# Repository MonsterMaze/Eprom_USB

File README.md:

# Eprom_USB
2716 through 27080 Eprom Programmer
A programmer for UV EPROMs with capacities between 2Kb (2716 series) and 1Mb (27C080 series).  
It uses an Arduino NANO and few other components.  
As a starting point I used the excelent [EpromProgrammer_ciprian-stingu](https://github.com/ciprian-stingu/EpromProgrammer) project

## Why this project?
I need write eproms for pinball machines and I have two not working
- Parallel port (epromwillem) windows XP 32b
- Serial port (PGM27) for DOS.

So, I need a new Eprom programmer with a USB port.
That is why I started this project
my OS is Ubuntu 24.04 - 64b right now.

## Main features
* It supports a large number of EPROMs with different capacities  
* 2 programming speeds (normal & fast). Fast programming speed is available if you configure the VCC correctly  
* On fast programming alghoritm, writing a 27C040 EPROM takes around 290 seconds  
* Error detection on writing  
* Additional verify option  

## GUI Software (Ubuntu Linux_x64)
Actualized "CMakeLists.txt" and code with AI help for Ubuntu 24.04 OS.  
New version 1.12 with 0.35v of voltage margin. (0.25v)
The complete source for project is in [soft_linux](soft_linux)  
I have compiled for Ubuntu 24.04 and is included in Release v1.12 folder [Release 1.12/AppImage](https://github.com/MonsterMaze/Eprom_USB/releases/download/Linux/Eprom_USB-x86_64.AppImage)  
With some changes for icons, locale, debug etc.  
Last version Linux  [soft_linux v2.26](soft_linux)  

## GUI Software (windows_x64)
Actualized "CMakeLists.txt" for Windows 11 OS.  
QTCreator project compiler with some few changes.  
The complete source for project is in [soft_Win64](soft_Win64)  
I have compiled in w11 and is included in Release v1.12 folder [Release 1.12/Eprom_USB_v1.0_Windows_x64.zip](https://github.com/MonsterMaze/Eprom_USB/releases/download/v1.12/Eprom_USB_v1.0_Windows_x64.zip)

## GUI Software (windows_x64) v2
I have some problems with serial Port in windows (!)  
so...  
Modify all project and name v2
The complete source for project is in [soft_Win64_v2](soft_Win64_v2)  
I have compiled in w11 and is included in Release v1.20 folder [Release 1.20/Eprom_USB_v2_Windows_x64.zip](https://github.com/MonsterMaze/Eprom_USB/releases/download/v1.12/Eprom_USB_v1.0_Windows_x64.zip)  
I test the exe in w7-64b and w11-64b.

## Eprom_USB v1.0.0 - Multiplatform Release
This release contains the standalone, portable binaries for the Eprom USB Programmer software,   
fully compatible with both Windows and Linux. No external installation or build tools are required.

### 🪟 Windows Instructions (64-bit)
1. Download **`Eprom_USB_v1.0_Windows_x64.zip`**.  
2. Extract the `.zip` file entirely into a folder of your choice.  
3. Double-click **`Eprom_USB.exe`** to launch the graphical interface.  
*Note: All required Qt, Gettext (`libintl`), and `libiconv` DLLs are included inside the package.*

### 🐧 Linux / Ubuntu Instructions (64-bit AppImage)
1. Download **`Eprom_USB-x86_64.AppImage`**.  
2. Open your terminal, navigate to the folder where you downloaded the file, and grant it execution permissions:  
   ```bash
   chmod +x Eprom_USB-x86_64.AppImage
   ```
3. Launch the application by double-clicking it or running:
   ```bash
   ./Eprom_USB-x86_64.AppImage
   ```

⚠️ **Important for Linux Users (Serial Port Permission):**
If the application cannot open or detect your USB serial port, your Linux user might lack dialout permissions.  
Fix this by running the following command once, then log out and log back into Ubuntu:
```bash
sudo usermod -a -G dialout \$USER
```

---
*Developed with Qt 5 and CMake. Built with native MinGW (Windows) and GCC (Linux) compiler suites.*

## Arduino Software
The sketch for arduino nano is here: [arduino_nano](arduino_nano)

## Hardware
New schematics and PCB into FreeCAD project, was modify for me are in [FreeCAD](FreeCAD) folder.  
I add LM317 for the Vpp power (12.5v - 12.75 - 21v - 25v) from 24Vac input  
For non KiCad users, schematics and PCB [hardware](hardware) in PDF format  
New v2 PCB made by Ivana, in PDF format [hardware/PCB_v2](hardware/PCB_v2) front, bottom and silk

## Images
The screenshots and images of PCB and others are available in [images](images) folder

## Supported EPROMs

### 2716 — 2 KB

| Manufacturer     | Part Number      |
|------------------|------------------|
| Generic          | 2716             |
| AMD              | 2716             |
| Intel            | 2716             |
| Hitachi          | HN462716         |
| Mitsubishi       | M5L2716K         |
| Fujitsu          | MBM2716          |
| Motorola         | MCM2716          |
| NEC              | µPD2716          |
| -                | ET2716           |
| -                | M2716            |

### 27C16 — 2 KB

| Manufacturer     | Part Number      |
|------------------|------------------|
| Generic          | 27C16            |
| National Semi    | 27C16            |
| AMD              | AM2716B          |
| National Semi    | NMC27C16B        |

### 2732 — 4 KB

| Manufacturer     | Part Number      |
|------------------|------------------|
| Generic          | 2732             |
| AMD              | AM2732           |
| AMD              | AM9732           |
| Fairchild        | F2732            |
| Hitachi          | HN462732         |
| Intel            | 2732A            |
| ST               | M2732A           |
| Fujitsu          | MBM2732          |
| NTE              | NTE2732A         |
| Toshiba          | TMM2732D         |
| NEC              | µPD2732A         |

### 27C32 — 4 KB

| Manufacturer     | Part Number      |
|------------------|------------------|
| Generic          | 27C32            |
| AMD              | AM2732B          |
| National Semi    | NMC27C32B        |
| WSI              | WS57C43C         |

### 2764 — 8 KB

| Manufacturer     | Part Number      |
|------------------|------------------|
| Generic          | 2764             |
| Intel            | 2764A            |
| ST               | M2764A           |
| Mitsubishi       | M5L2764K         |
| NTE              | NTE2764          |
| Toshiba          | TMM2764AD        |

### 27C64 — 8 KB

| Manufacturer     | Part Number      |
|------------------|------------------|
| Generic          | 27C64            |
| Microchip        | 27C64            |
| Cypress          | Cy7C266          |
| Fujitsu          | MBM27C64         |
| National Semi    | NMC27C64         |
| Texas Instruments| TMS27C64         |

### 27128 — 16 KB

| Manufacturer     | Part Number      |
|------------------|------------------|
| Generic          | 27128            |
| Hitachi          | HN4827128G       |
| Hitachi          | HN27128          |
| Intel            | M27128A          |
| ST               | M27128A          |
| Mitsubishi       | M5L27128K        |
| Mitsubishi       | M5M27C128K       |
| Fujitsu          | MBM27128         |
| NTE              | NTE21128         |
| Toshiba          | TMM27128AD       |
| Texas Instruments| TMS27128         |
| NEC              | µPD27128         |

### 27C128 — 16 KB

| Manufacturer     | Part Number      |
|------------------|------------------|
| Generic          | 27C128           |
| Microchip        | 27C128           |
| AMD              | AM27C128         |
| Atmel            | AT27C128         |
| Cypress          | CY27C128         |
| Sharp            | LH57126          |
| ST               | M27C128          |
| Oki              | MSM27C128        |
| Fairchild        | NM27C128         |
| National Semi    | NM27C128         |
| -                | QP27C128         |
| Texas Instruments| SMJ27C128        |
| Texas Instruments| TMS27C128        |

### 27256 — 32 KB

| Manufacturer     | Part Number      |
|------------------|------------------|
| Generic          | 27256            |
| -                | A68C256          |
| Atmel            | AT27256          |
| Intel            | 27256            |
| Mitsubishi       | M5L27256K        |
| Fujitsu          | MBM27256         |
| Oki              | MSM27256         |
| Toshiba          | TMM27256         |
| NEC              | µPD27256         |

### 27C256 — 32 KB

| Manufacturer     | Part Number      |
|------------------|------------------|
| Generic          | 27C256           |
| Microchip        | 27C256           |
| AMD              | AM27C256         |
| AMD              | AM27H256         |
| Sony             | CXK27C256DQ      |
| Cypress          | CY27C256         |
| Cypress          | CY27H256         |
| Cypress          | CY7C274          |
| -                | EM27C256         |
| -                | FM27C256         |
| Hitachi          | HN27C256A        |
| Hitachi          | HN27C256AG       |
| ISSI             | IS27C256         |
| ST               | M27C256B         |
| Mitsubishi       | M5M27C256K       |
| Fujitsu          | MBM27C256        |
| -                | 27HC256          |
| Oki              | MSM27C256H       |
| Fairchild        | NM27C256         |
| National Semi    | NM27C256         |
| National Semi    | NM27LC256        |
| National Semi    | NMC27C256        |
| National Semi    | NMC87C257        |
| -                | NPX27C256        |
| -                | QP27C256         |
| SEEQ             | 27C256           |
| SEEQ             | M27C256          |
| ASI              | SMJ27C256        |
| Texas Instruments| SMJ27C256        |
| -                | SPM27C256        |
| Toshiba          | TC57256          |
| Texas Instruments| TMS27C256        |
| Texas Instruments| TMS87C257        |
| NEC              | µPD27C256        |

### 27512 — 64 KB

| Manufacturer     | Part Number      |
|------------------|------------------|
| Generic          | 27512            |
| Intel            | 27512            |
| AMD              | AM27512          |
| Hitachi          | HN27512          |
| ST               | M27512           |
| Mitsubishi       | M5L27512K        |
| Oki              | MSM27512         |
| Toshiba          | TMM27512AD       |

### 27C512 — 64 KB

| Manufacturer     | Part Number      |
|------------------|------------------|
| Generic          | 27C512           |
| Microchip        | 27C512           |
| Intel            | 27C512           |
| Philips          | 27C512           |
| AMD              | AM27C512         |
| Sony             | CXK27C512DQ      |
| Cypress          | CY27C512         |
| Cypress          | CY27H512         |
| -                | EM27C512         |
| -                | FM27C512         |
| Hitachi          | HN27C512         |
| ISSI             | IS27HC512        |
| Fujitsu          | MBM27C512        |
| Macronix         | MX27C512         |
| National Semi    | NM27C512         |
| National Semi    | NM27P512         |
| ASI              | SMJ27C512        |
| Texas Instruments| SMJ27C512        |
| Toshiba          | TC57512AD        |
| Texas Instruments| TMS27C512        |
| NEC              | µPD27C512        |

### 27C010 — 128 KB

| Manufacturer     | Part Number      |
|------------------|------------------|
| Generic          | 27C010           |
| AMD              | AM27C010         |
| AMD              | AM27H010         |
| AMD              | AM27HB010        |
| Cypress          | CY27C010         |
| Cypress          | CY27H010         |
| Intel            | 27C010           |
| -                | EM27C010         |
| -                | FM27C010         |
| Hitachi          | HN27C101         |
| ISSI             | IS27C010         |
| Mitsubishi       | M5M27C101K       |
| Fairchild        | NM27C010         |
| National Semi    | NM27C010         |
| National Semi    | NMC27C010        |
| ASI              | SMJ27C010        |
| Texas Instruments| SMJ27C010        |
| Texas Instruments| TMS27C010        |

### 27C1001 — 128 KB

| Manufacturer     | Part Number      |
|------------------|------------------|
| Generic          | 27C1001          |
| Sony             | CXK27C1001DQ     |
| ST               | M27C1001         |
| Fujitsu          | MBM27C1001       |
| Oki              | MSM27C1000       |
| Macronix         | MX27C1000        |
| Toshiba          | TC57C1001        |
| Toshiba          | TC57H1001        |

### 27C020 — 256 KB

| Manufacturer     | Part Number      |
|------------------|------------------|
| Generic          | 27C020           |
| AMD              | AM27C020         |
| Cypress          | CY27C020         |
| Intel            | 27C020           |
| -                | EM27C020         |
| ISSI             | IS27C020         |
| National Semi    | NM27C020         |
| Texas Instruments| TMS27C020        |

### 27C2001 — 256 KB

| Manufacturer     | Part Number      |
|------------------|------------------|
| Generic          | 27C2001          |
| ST               | M27C2001         |
| Oki              | MSM27C2000       |
| NEC              | µPD27C2001       |

### 27C040 — 512 KB

| Manufacturer     | Part Number      |
|------------------|------------------|
| Generic          | 27C040           |
| AMD              | AM27C040         |
| Cypress          | CY27C040         |
| -                | EM27C040         |
| -                | FM27C040         |
| Intel            | 27C040           |
| National Semi    | NM27C040         |
| NXP              | NXP27C040        |
| ASI              | SMJ27C040        |
| Micross          | SMJ27C040        |
| Texas Instruments| SMJ27C040        |
| Texas Instruments| TMS27C040        |

### 27C4001 — 512 KB

| Manufacturer     | Part Number      |
|------------------|------------------|
| Generic          | 27C4001          |
| Hitachi          | HN27C4001        |
| ST               | M27C4001         |
| Fujitsu          | MBM27C4001       |
| Oki              | MSM27C401        |
| Macronix         | MX27C4000        |
| Toshiba          | TC57C4000        |
| NEC              | µPD27C4001       |

### 27C080 — 1024 KB (1 MB)

| Manufacturer     | Part Number      |
|------------------|------------------|
| Generic          | 27C080           |
| AMD              | AM27C080         |
| Atmel            | AT27LV080        |
| ST               | M27C801          |
| Macronix         | MX27C8000        |

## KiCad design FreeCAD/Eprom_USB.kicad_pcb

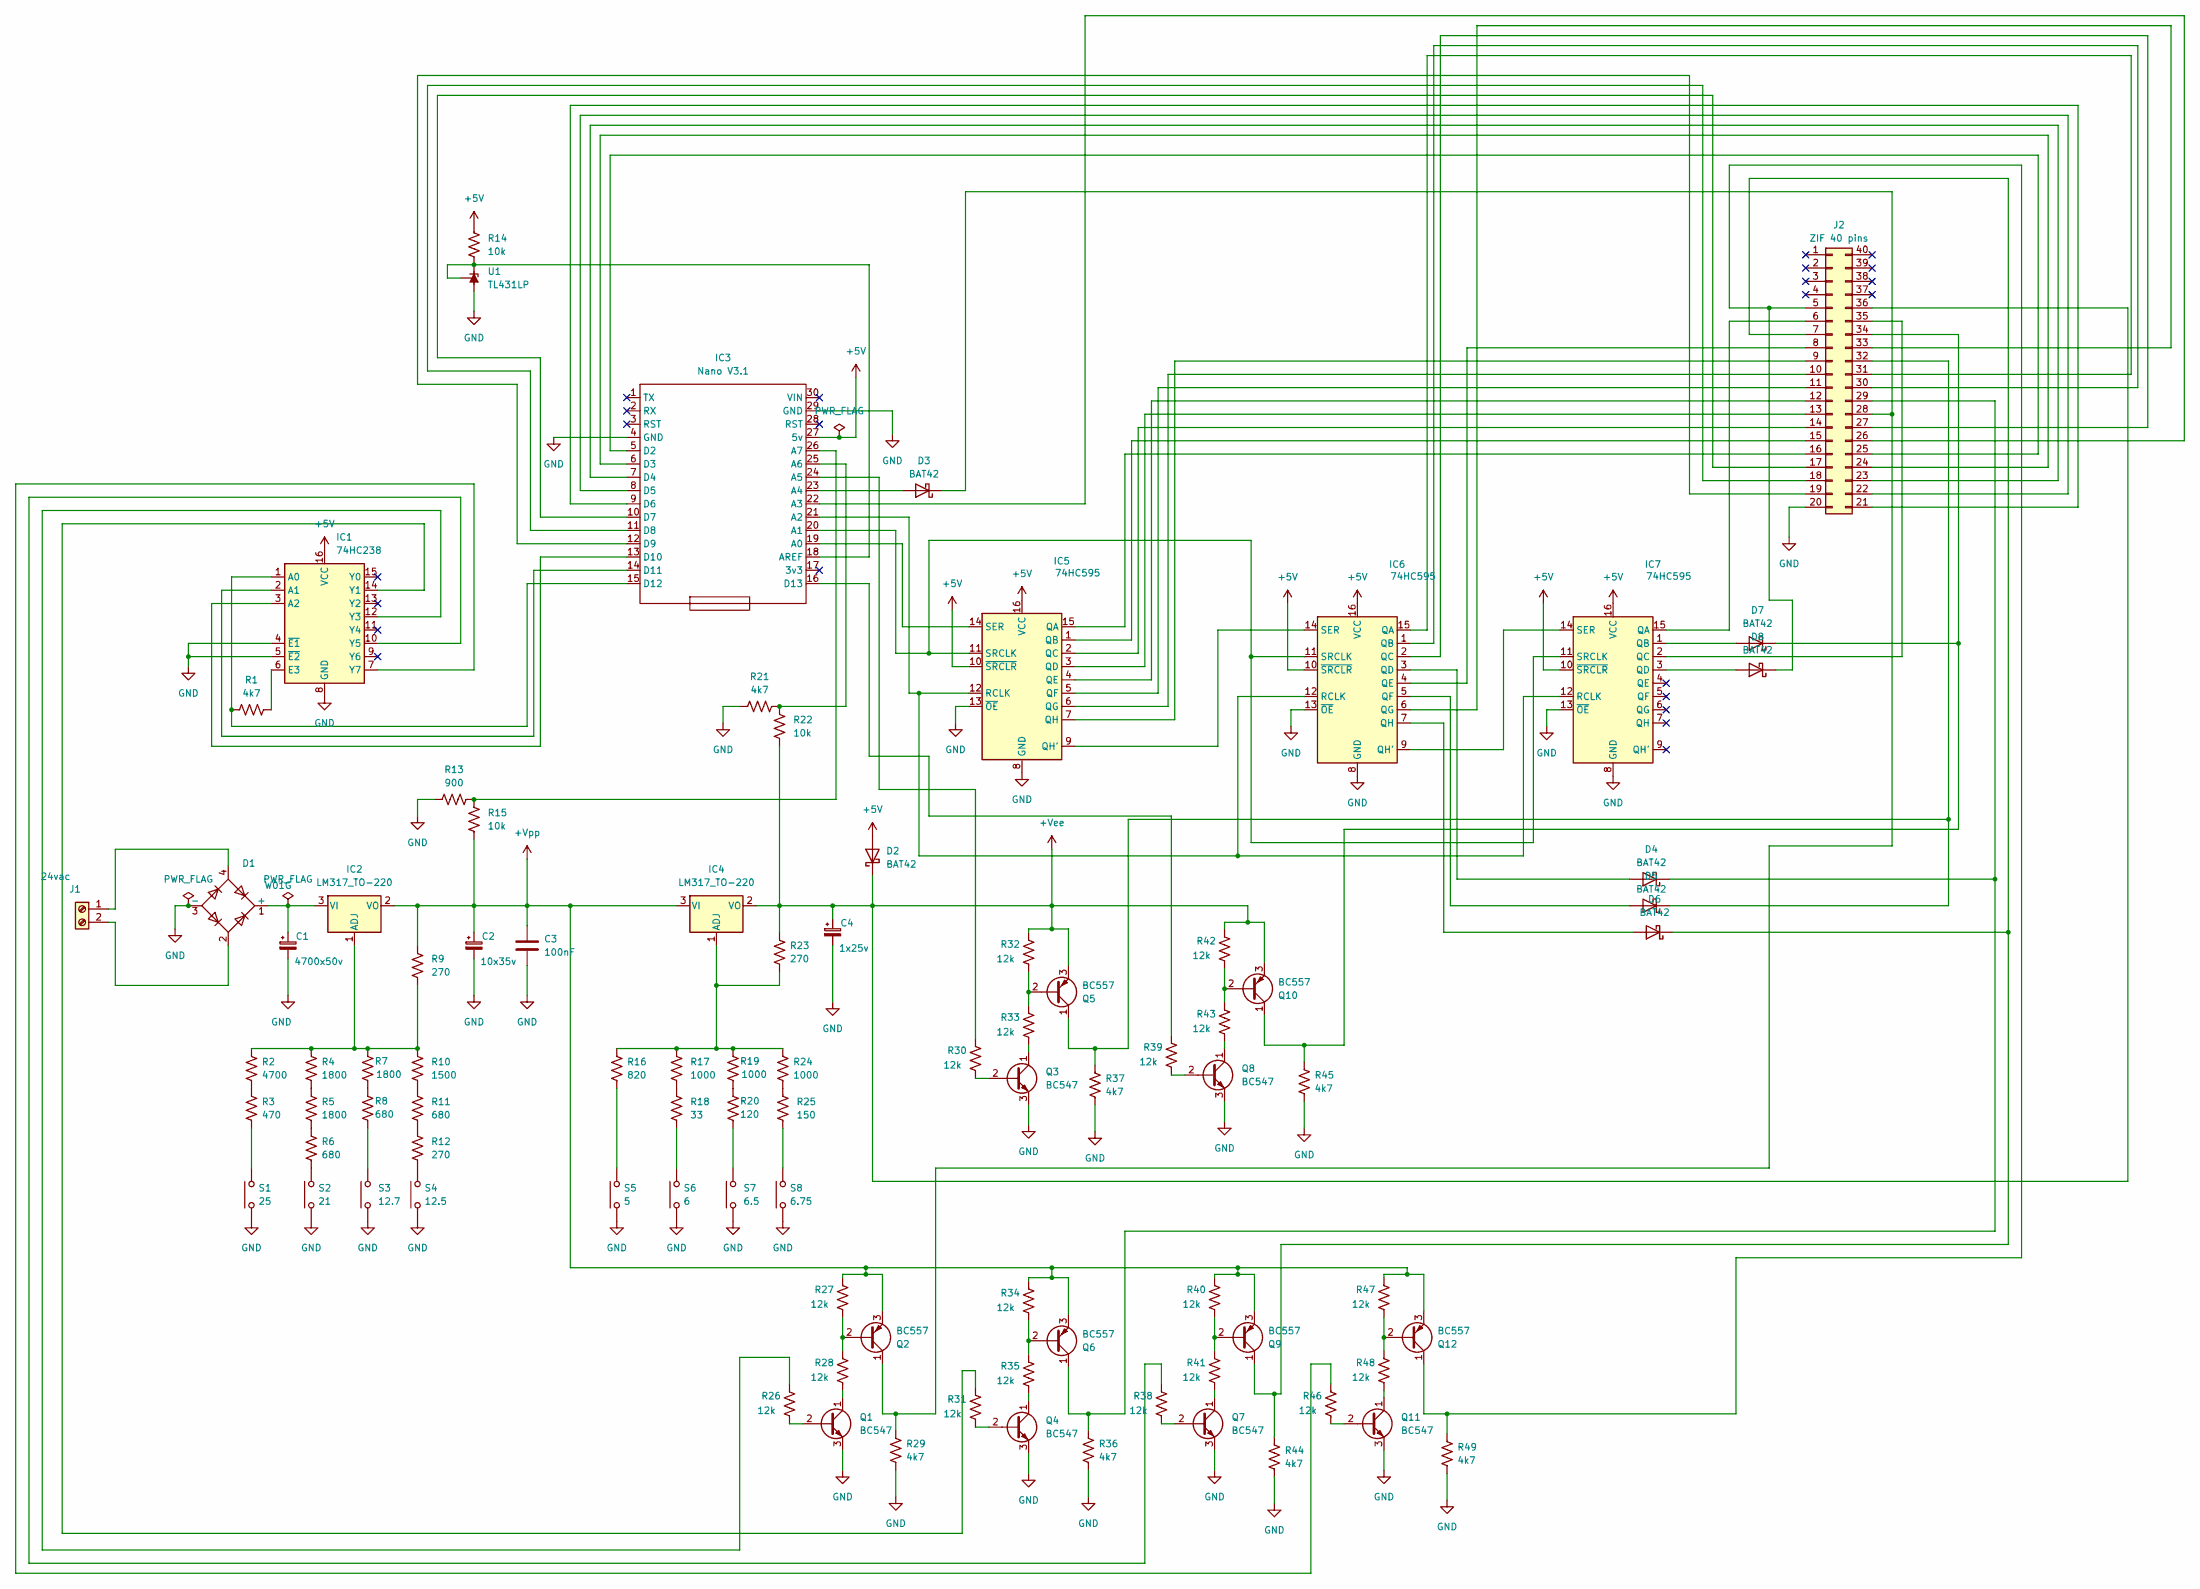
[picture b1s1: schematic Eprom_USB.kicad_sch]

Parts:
C1: 4700x50v; CP_Radial_D18.0mm_P7.50mm
C2: 10x35v; CP_Radial_D6.3mm_P2.50mm
C3: 100nF; C_Disc_D5.0mm_W2.5mm_P5.00mm
C4: 1x25v; CP_Radial_D6.3mm_P2.50mm
D1: W01G; Diode_Bridge_Round_D9.8mm
D2, D3, D4, D5, D6, D7, D8: BAT42; D_DO-35_SOD27_P7.62mm_Horizontal
IC1: 74HC238; DIP-16_W7.62mm
IC2, IC4: LM317_TO-220; TO-220-3_Vertical
IC3: Nano V3.1; Arduino_Nano
IC5, IC6, IC7: 74HC595; DIP-16_W7.62mm
J1: 24vac; TerminalBlock_Phoenix_MKDS-1,5-2_1x02_P5.00mm_Horizontal
J2: ZIF 40 pins; DIP_Socket-40_W11.9mm_W12.7mm_W15.24mm_W17.78mm_W18.5mm_3M_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
Q1, Q3, Q4, Q7, Q8, Q11: BC547; TO-92_Inline
Q2, Q5, Q6, Q9, Q10, Q12: BC557; TO-92_Inline
R1, R21, R29, R36, R37, R44, R45, R49: 4k7; R_Axial_DIN0204_L3.6mm_D1.6mm_P7.62mm_Horizontal
R2: 4700; R_Axial_DIN0204_L3.6mm_D1.6mm_P7.62mm_Horizontal
R3: 470; R_Axial_DIN0204_L3.6mm_D1.6mm_P7.62mm_Horizontal
R4, R5, R7: 1800; R_Axial_DIN0204_L3.6mm_D1.6mm_P7.62mm_Horizontal
R6, R8, R11: 680; R_Axial_DIN0204_L3.6mm_D1.6mm_P7.62mm_Horizontal
R9, R12, R23: 270; R_Axial_DIN0204_L3.6mm_D1.6mm_P7.62mm_Horizontal
R10: 1500; R_Axial_DIN0204_L3.6mm_D1.6mm_P7.62mm_Horizontal
R13: 900; R_Axial_DIN0204_L3.6mm_D1.6mm_P7.62mm_Horizontal
R14, R15, R22: 10k; R_Axial_DIN0204_L3.6mm_D1.6mm_P7.62mm_Horizontal
R16: 820; R_Axial_DIN0204_L3.6mm_D1.6mm_P7.62mm_Horizontal
R17, R19, R24: 1000; R_Axial_DIN0204_L3.6mm_D1.6mm_P7.62mm_Horizontal
R18: 33; R_Axial_DIN0204_L3.6mm_D1.6mm_P7.62mm_Horizontal
R20: 120; R_Axial_DIN0204_L3.6mm_D1.6mm_P7.62mm_Horizontal
R25: 150; R_Axial_DIN0204_L3.6mm_D1.6mm_P7.62mm_Horizontal
R26, R27, R28, R30, R31, R32, R33, R34, R35, R38, R39, R40, R41, R42, R43, R46, R47, R48: 12k; R_Axial_DIN0204_L3.6mm_D1.6mm_P7.62mm_Horizontal
S1: 25; PinHeader_1x02_P2.54mm_Vertical
S2: 21; PinHeader_1x02_P2.54mm_Vertical
S3: 12.7; PinHeader_1x02_P2.54mm_Vertical
S4: 12.5; PinHeader_1x02_P2.54mm_Vertical
S5: 5; PinHeader_1x02_P2.54mm_Vertical
S6: 6; PinHeader_1x02_P2.54mm_Vertical
S7: 6.5; PinHeader_1x02_P2.54mm_Vertical
S8: 6.75; PinHeader_1x02_P2.54mm_Vertical
U1: TL431LP; TO-92_Inline

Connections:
+5V: D2.2 (A), IC1.16 (VCC), IC3.27 (5v), IC5.10 (~SRCLR), IC5.16 (VCC), IC6.10 (~SRCLR), IC6.16 (VCC), IC7.10 (~SRCLR), IC7.16 (VCC), R14.2
+Vee: C4.1, D2.1 (K), IC4.2 (VO), J2.36, Q5.3 (E), Q10.3 (E), R22.1, R23.2, R32.2, R42.2
+Vpp: C2.1, C3.1, IC2.2 (VO), IC4.3 (VI), Q2.3 (E), Q6.3 (E), Q9.3 (E), Q12.3 (E), R9.2, R15.1, R27.2, R34.2, R40.2, R47.2
GND: C1.2, C2.2, C3.2, C4.2, D1.3 (-), IC1.4 (~E1), IC1.5 (~E2), IC1.8 (GND), IC3.4 (GND), IC3.29 (GND), IC5.8 (GND), IC5.13 (~OE), IC6.8 (GND), IC6.13 (~OE), IC7.8 (GND), IC7.13 (~OE), J2.20, Q1.3 (E), Q3.3 (E), Q4.3 (E), Q7.3 (E), Q8.3 (E), Q11.3 (E), R13.2, R21.2, R29.1, R36.1, R37.1, R44.1, R45.1, R49.1, S1.1, S2.1, S3.1, S4.1, S5.1, S6.1, S7.1, S8.1, U1.2 (A)
unnamed: C1.1, D1.1 (+), IC2.3 (VI)
unnamed: D3.2 (A), IC3.23 (A4)
unnamed: D3.1 (K), J2.28, Q2.1 (C), R29.2
unnamed: D4.2 (A), IC6.3 (QD)
unnamed: D4.1 (K), J2.29, Q6.1 (C), R36.2
unnamed: D5.2 (A), IC6.5 (QF)
unnamed: D5.1 (K), J2.32, Q5.1 (C), R37.2
unnamed: D6.2 (A), IC6.7 (QH)
unnamed: D6.1 (K), J2.7, Q9.1 (C), R44.2
unnamed: D7.2 (A), IC7.1 (QB)
unnamed: D7.1 (K), J2.34, Q10.1 (C), R45.2
unnamed: D8.2 (A), IC7.3 (QD)
unnamed: D8.1 (K), J2.5, Q12.1 (C), R49.2
unnamed: IC1.1 (A0), IC3.15 (D12), R1.2
unnamed: IC1.2 (A1), IC3.14 (D11)
unnamed: IC1.3 (A2), IC3.13 (D10)
unnamed: IC1.6 (E3), R1.1
unnamed: IC1.14 (Y1), R31.2
unnamed: IC1.12 (Y3), R26.2
unnamed: IC1.10 (Y5), R38.2
unnamed: IC1.7 (Y7), R46.2
unnamed: IC2.1 (ADJ), R2.2, R4.2, R7.2, R9.1, R10.2
unnamed: IC3.19 (A0), IC5.14 (SER)
unnamed: IC3.20 (A1), IC5.11 (SRCLK), IC6.11 (SRCLK), IC7.11 (SRCLK)
unnamed: IC3.21 (A2), IC5.12 (RCLK), IC6.12 (RCLK), IC7.12 (RCLK)
unnamed: IC3.22 (A3), J2.26
unnamed: IC3.24 (A5), R30.2
unnamed: IC3.25 (A6), R21.1, R22.2
unnamed: IC3.26 (A7), R13.1, R15.2
unnamed: IC3.18 (AREF), R14.1, U1.1 (REF), U1.3 (K)
unnamed: IC3.5 (D2), J2.25
unnamed: IC3.6 (D3), J2.24
unnamed: IC3.7 (D4), J2.23
unnamed: IC3.8 (D5), J2.22
unnamed: IC3.9 (D6), J2.21
unnamed: IC3.10 (D7), J2.17
unnamed: IC3.11 (D8), J2.18
unnamed: IC3.12 (D9), J2.19
unnamed: IC3.16 (D13), R39.2
unnamed: IC4.1 (ADJ), R16.2, R17.2, R19.2, R23.1, R24.2
unnamed: IC5.15 (QA), J2.16
unnamed: IC5.1 (QB), J2.15
unnamed: IC5.2 (QC), J2.14
unnamed: IC5.3 (QD), J2.13
unnamed: IC5.4 (QE), J2.12
unnamed: IC5.5 (QF), J2.11
unnamed: IC5.6 (QG), J2.10
unnamed: IC5.9 (QH'), IC6.14 (SER)
unnamed: IC5.7 (QH), J2.9
unnamed: IC6.15 (QA), J2.31
unnamed: IC6.1 (QB), J2.30
unnamed: IC6.2 (QC), J2.27
unnamed: IC6.4 (QE), J2.8
unnamed: IC6.6 (QG), J2.33
unnamed: IC6.9 (QH'), IC7.14 (SER)
unnamed: IC7.15 (QA), J2.6
unnamed: IC7.2 (QC), J2.35
unnamed: D1.4, J1.1
unnamed: D1.2, J1.2
unnamed: Q1.2 (B), R26.1
unnamed: Q1.1 (C), R28.1
unnamed: Q2.2 (B), R27.1, R28.2
unnamed: Q3.2 (B), R30.1
unnamed: Q3.1 (C), R33.1
unnamed: Q4.2 (B), R31.1
unnamed: Q4.1 (C), R35.1
unnamed: Q5.2 (B), R32.1, R33.2
unnamed: Q6.2 (B), R34.1, R35.2
unnamed: Q7.2 (B), R38.1
unnamed: Q7.1 (C), R41.1
unnamed: Q8.2 (B), R39.1
unnamed: Q8.1 (C), R43.1
unnamed: Q9.2 (B), R40.1, R41.2
unnamed: Q10.2 (B), R42.1, R43.2
unnamed: Q11.2 (B), R46.1
unnamed: Q11.1 (C), R48.1
unnamed: Q12.2 (B), R47.1, R48.2
unnamed: R2.1, R3.2
unnamed: R3.1, S1.2
unnamed: R4.1, R5.2
unnamed: R5.1, R6.2
unnamed: R6.1, S2.2
unnamed: R7.1, R8.2
unnamed: R8.1, S3.2
unnamed: R10.1, R11.2
unnamed: R11.1, R12.2
unnamed: R12.1, S4.2
unnamed: R16.1, S5.2
unnamed: R17.1, R18.2
unnamed: R18.1, S6.2
unnamed: R19.1, R20.2
unnamed: R20.1, S7.2
unnamed: R24.1, R25.2
unnamed: R25.1, S8.2

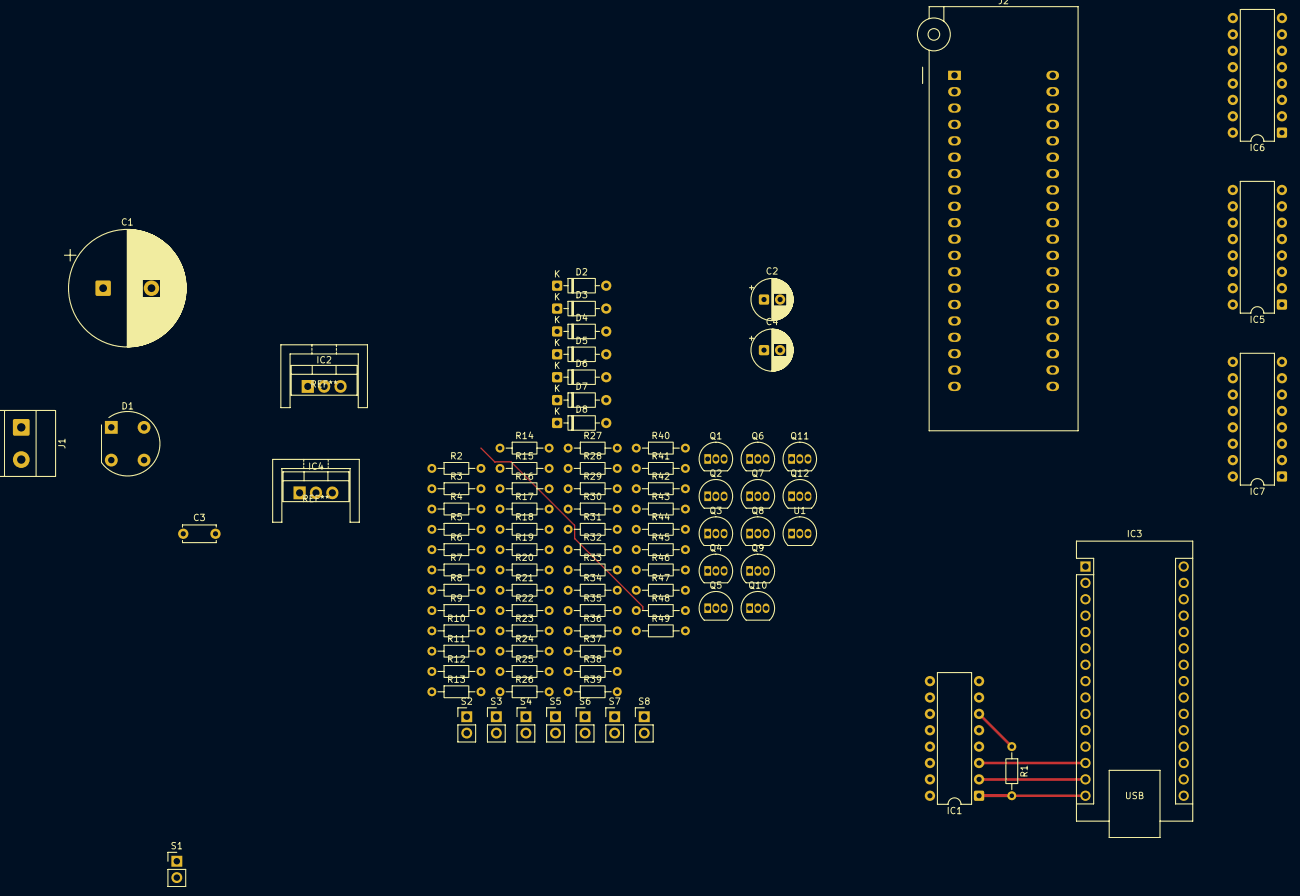
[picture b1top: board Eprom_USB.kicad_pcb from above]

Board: 2 copper layers, 91 parts (0 on the bottom side), 98 nets.
